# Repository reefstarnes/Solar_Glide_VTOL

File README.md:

# Solar_Glide_VTOL
Senior Capstone

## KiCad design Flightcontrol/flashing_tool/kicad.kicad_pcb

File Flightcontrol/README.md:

# Flight control
Flight Controller:

Flasher4OTG:

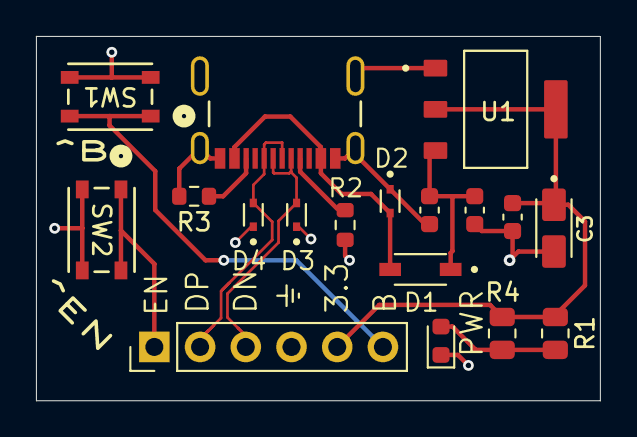
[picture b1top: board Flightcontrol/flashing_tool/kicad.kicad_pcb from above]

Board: 2 copper layers, 31.3 x 20.2 mm, 18 parts (0 on the bottom side), 11 nets.

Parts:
C1, C4: 0.1uF; C_0603_1608Metric
C2: 10uF; C_0603_1608Metric
C3: 22uF; CAPMP3216X180N
D1: 1N5819HW-7-F; SOD3715X145N
D2, D3, D4: LESD5D5.0CT1G; TVS_LESD5D5.0CT1G
J1: 2171790001; MOLEX_2171790001
J2: Conn_01x06_Pin; PinHeader_1x06_P2.54mm_Vertical
PWR: LED; LED_0603_1608Metric
R1, R4: 560; R_0805_2012Metric
R2, R3: 5.1k; R_0603_1608Metric
SW1, SW2: PTS815 SJM 250 SMTR LFS; GSPTS0020
U1: AMS1117-3.3; SOT229P700X180-4N

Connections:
/3.3: C3.1, C4.1, J2.5, R1.1, R4.1, U1.2 (VOUT)
/D+: D4.2, J1.A6 (DP1), J1.B6 (DP2), J2.2
/D-: D3.2, J1.A7 (DN1), J1.B7 (DN2), J2.3
/S1: J2.1, SW2.1, SW2.2
/S2: J2.6, SW1.1, SW1.2
/VCC_5V: C1.1, C2.1, D1.C, U1.3 (VIN)
GND: C1.2, C2.2, C3.2, C4.2, D2.1, D3.1, D4.1, J1.A1B12 (GND1), J1.B1A12 (GND2), J1.SH1 (SHIELD1), J1.SH2 (SHIELD2), J1.SH3 (SHIELD3), J1.SH4 (SHIELD4), J2.4, PWR.1 (K), R2.2, R3.2, SW1.3, SW1.4, SW2.3, SW2.4, U1.1 (GND/ADJ)
unnamed: PWR.2 (A), R1.2, R4.2
unnamed: J1.A5 (CC1), R2.1
unnamed: J1.B5 (CC2), R3.1
unnamed: D1.A, D2.2, J1.A4B9 (VBUS1), J1.B4A9 (VBUS2)

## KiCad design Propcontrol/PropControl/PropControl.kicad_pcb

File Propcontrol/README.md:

# Prop control
Prop control block

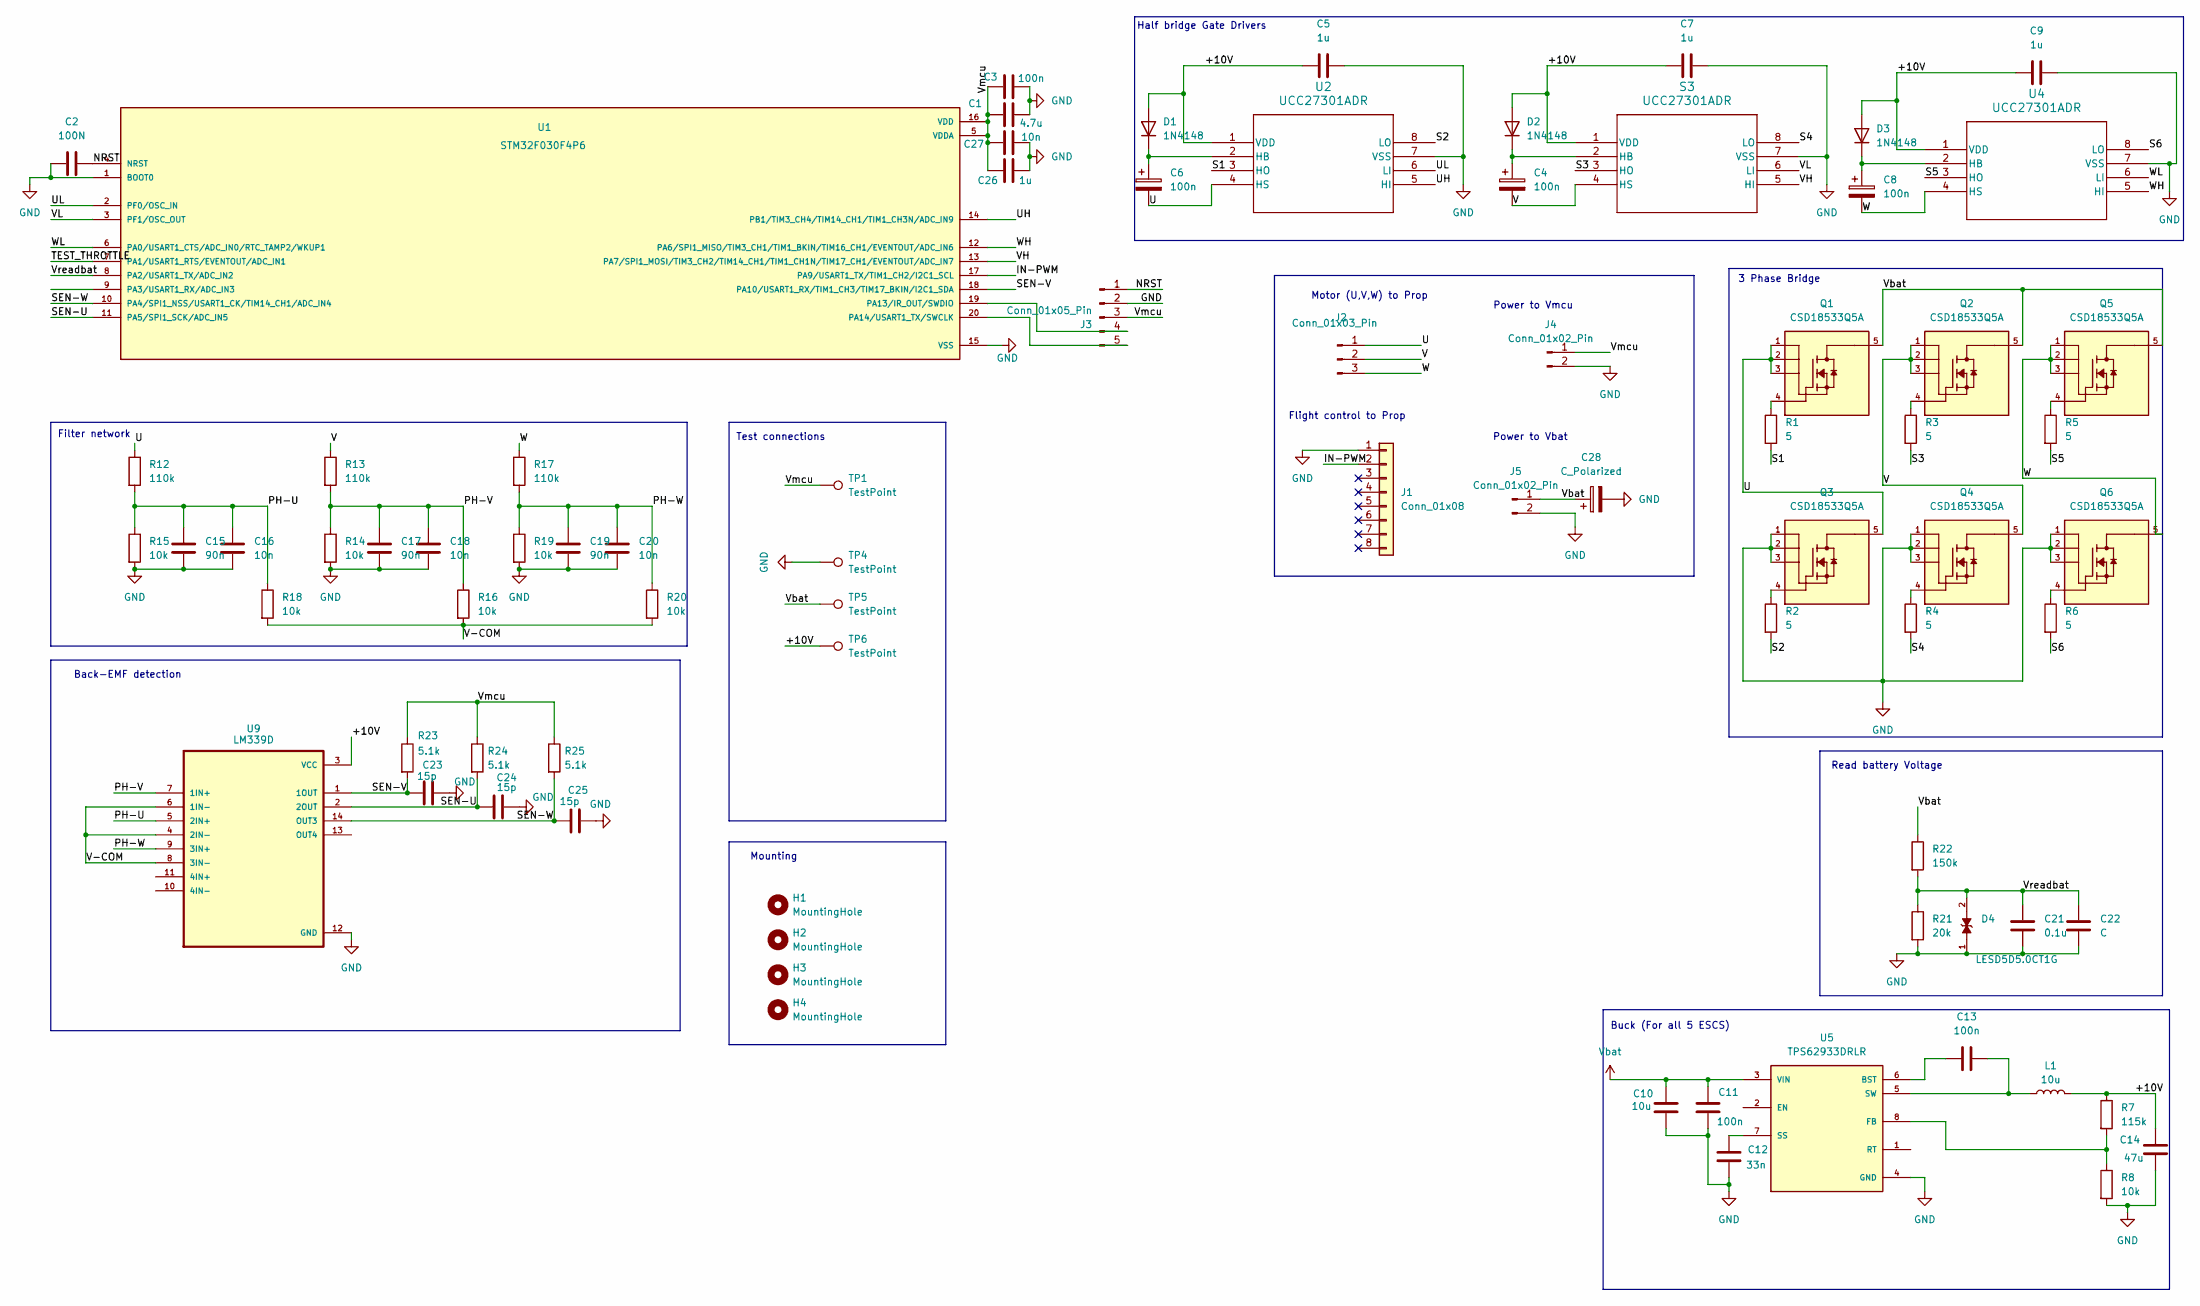
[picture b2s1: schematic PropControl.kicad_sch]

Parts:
C1: 4.7u; C_0603_1608Metric
C2: 100N; C_0603_1608Metric
C3: 100n; CAPC1608X90 100nF
C4, C6, C8, C11, C13: 100n; C_0603_1608Metric
C5, C7, C9, C27: 1u; C_0603_1608Metric
C10: 10u; C_0603_1608Metric
C12: 33n; C_1206_3216Metric
C14: 47u; C_1206_3216Metric
C15, C17, C19: 90n; CAPC1608X90 100nF
C16, C18, C20, C26: 10n; CAPC1608X90N 10nF
C21: 0.1u; C_0603_1608Metric
C22: C; C_0603_1608Metric
C23, C24, C25: 15p; C_0603_1608Metric
C28: C_Polarized; CP_Radial_D12.5mm_P5.00mm
D1, D2, D3: 1N4148; D_DO-35_SOD27_P7.62mm_Horizontal
D4: LESD5D5.0CT1G; TVS_LESD5D5.0CT1G; PARTREV O
H1, H2, H3, H4: MountingHole; MountingHole_2.2mm_M2
J1: Conn_01x08; CONN_SM06B-GHS-TB_JST
J2: Conn_01x03_Pin; MR60PW-M
J3: Conn_01x05_Pin; PinHeader_1x05_P2.54mm_Vertical
J4: Conn_01x02_Pin; JST_PH_B2B-PH-K_1x02_P2.00mm_Vertical
J5: Conn_01x02_Pin; AMASS_XT60-M_1x02_P7.20mm_Vertical
L1: 10u; L_0805_2012Metric
Q1, Q2, Q3, Q4, Q5, Q6: CSD18533Q5A; VSON-8_3.3x3.3mm_P0.65mm_NexFET; PARTREV B
R1, R2, R3, R4, R5, R6: 5; R_0603_1608Metric
R7: 115k; R_0805_2012Metric
R8, R14, R15, R16, R18, R19, R20: 10k; R_0603_1608Metric
R12, R13, R17: 110k; R_1206_3216Metric
R21: 20k; R_0603_1608Metric
R22: 150k; R_0603_1608Metric
R23, R24, R25: 5.1k; R_0603_1608Metric
S3: UCC27301ADR; SOIC8_D_TEX
TP1, TP4, TP5, TP6: TestPoint; TestPoint_Pad_D1.5mm
U1: STM32F030F4P6; SOP65P640X120-20N
U2, U4: UCC27301ADR; SOIC8_D_TEX
U5: TPS62933DRLR; SOTFL50P160X60-8N; PARTREV D
U9: LM339D; SOIC127P600X175-14N

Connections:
/+10V: C5.1, C7.1, C9.1, C14.1, D1.2 (A), D2.2 (A), D3.2 (A), L1.2, R7.1, S3.1 (VDD), TP6.1, U2.1 (VDD), U4.1 (VDD), U9.3 (VCC)
/IN-PWM: J1.2, U1.17 (PA9/USART1_TX/TIM1_CH2/I2C1_SCL)
/NRST: C2.2, J3.1, U1.4 (NRST)
/PH-U: C15.1, C16.1, R12.2, R15.1, R18.1, U9.5 (2IN+)
/PH-V: C17.1, C18.1, R13.2, R14.1, R16.1, U9.7 (1IN+)
/PH-W: C19.1, C20.1, R17.2, R19.1, R20.1, U9.9 (3IN+)
/S1: R1.2, U2.3 (HO)
/S2: R2.2, U2.8 (LO)
/S3: R3.2, S3.3 (HO)
/S4: R4.2, S3.8 (LO)
/S5: R5.2, U4.3 (HO)
/S6: R6.2, U4.8 (LO)
/SEN-U: C24.1, R24.2, U1.11 (PA5/SPI1_SCK/ADC_IN5), U9.2 (2OUT)
/SEN-V: C23.1, R23.2, U1.18 (PA10/USART1_RX/TIM1_CH3/TIM17_BKIN/I2C1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), U9.1 (1OUT)
/SEN-W: C25.1, R25.2, U1.10 (PA4/SPI1_NSS/USART1_CK/TIM14_CH1/ADC_IN4), U9.14 (OUT3)
/TEST_THROTTLE: U1.7 (PA1/USART1_RTS/EVENTOUT/ADC_IN1)
/U: C6.2, J2.1, Q1.1, Q1.2, Q1.3, Q3.5, R12.1, U2.4 (HS)
/UH: U1.14 (PB1/TIM3_CH4/TIM14_CH1/TIM1_CH3N/ADC_IN9), U2.5 (HI)
/UL: U1.2 (PF0/OSC_IN), U2.6 (LI)
/V: C4.2, J2.2, Q2.1, Q2.2, Q2.3, Q4.5, R13.1, S3.4 (HS)
/V-COM: R16.2, R18.2, R20.2, U9.4 (2IN-), U9.6 (1IN-), U9.8 (3IN-)
/VH: S3.5 (HI), U1.13 (PA7/SPI1_MOSI/TIM3_CH2/TIM14_CH1/TIM1_C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)
/VL: S3.6 (LI), U1.3 (PF1/OSC_OUT)
/Vmcu: C1.1, C3.1, C26.1, C27.1, J3.3, J4.1, R23.1, R24.1, R25.1, TP1.1, U1.5 (VDDA), U1.16 (VDD)
/Vreadbat: C21.1, C22.1, D4.2, R21.1, R22.2, U1.8 (PA2/USART1_TX/ADC_IN2)
/W: C8.2, J2.3, Q5.1, Q5.2, Q5.3, Q6.5, R17.1, U4.4 (HS)
/WH: U1.12 (PA6/SPI1_MISO/TIM3_CH1/TIM1_BKIN/TIM16_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), U4.5 (HI)
/WL: U1.6 (PA0/USART1_CTS/ADC_IN0/RTC_TAMP2/WKUP1), U4.6 (LI)
GND: C1.2, C2.1, C3.2, C5.2, C7.2, C9.2, C10.2, C11.2, C12.2, C14.2, C15.2, C16.2, C17.2, C18.2, C19.2, C20.2, C21.2, C22.2, C23.2, C24.2, C25.2, C26.2, C27.2, C28.2, D4.1, J1.1, J3.2, J4.2, J5.2, Q3.1, Q3.2, Q3.3, Q4.1, Q4.2, Q4.3, Q6.1, Q6.2, Q6.3, R8.2, R14.2, R15.2, R19.2, R21.2, S3.7 (VSS), TP4.1, U1.1 (BOOT0), U1.15 (VSS), U2.7 (VSS), U4.7 (VSS), U5.4 (GND), U9.12 (GND)
unnamed: C6.1, D1.1 (K), U2.2 (HB)
unnamed: C4.1, D2.1 (K), S3.2 (HB)
unnamed: C8.1, D3.1 (K), U4.2 (HB)
unnamed: J3.4, U1.19 (PA13/IR_OUT/SWDIO)
unnamed: J3.5, U1.20 (PA14/USART1_TX/SWCLK)
unnamed: Q1.4, R1.1
unnamed: Q2.4, R3.1
unnamed: Q3.4, R2.1
unnamed: Q4.4, R4.1
unnamed: Q5.4, R5.1
unnamed: Q6.4, R6.1
unnamed: C13.1, U5.6 (BST)
unnamed: R7.2, R8.1, U5.8 (FB)
unnamed: C12.1, U5.7 (SS)
unnamed: C13.2, L1.1, U5.5 (SW)
Vbat: C10.1, C11.1, C28.1, J5.1, Q1.5, Q2.5, Q5.5, R22.1, TP5.1, U5.3 (VIN)

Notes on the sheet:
Flight control to Prop
Power to Vmcu
Mounting
Power to Vbat
Test connections
Half bridge Gate Drivers
Buck (For all 5 ESCS)
3 Phase Bridge
Back-EMF detection
Motor (U,V,W) to Prop
Read battery Voltage
Filter network

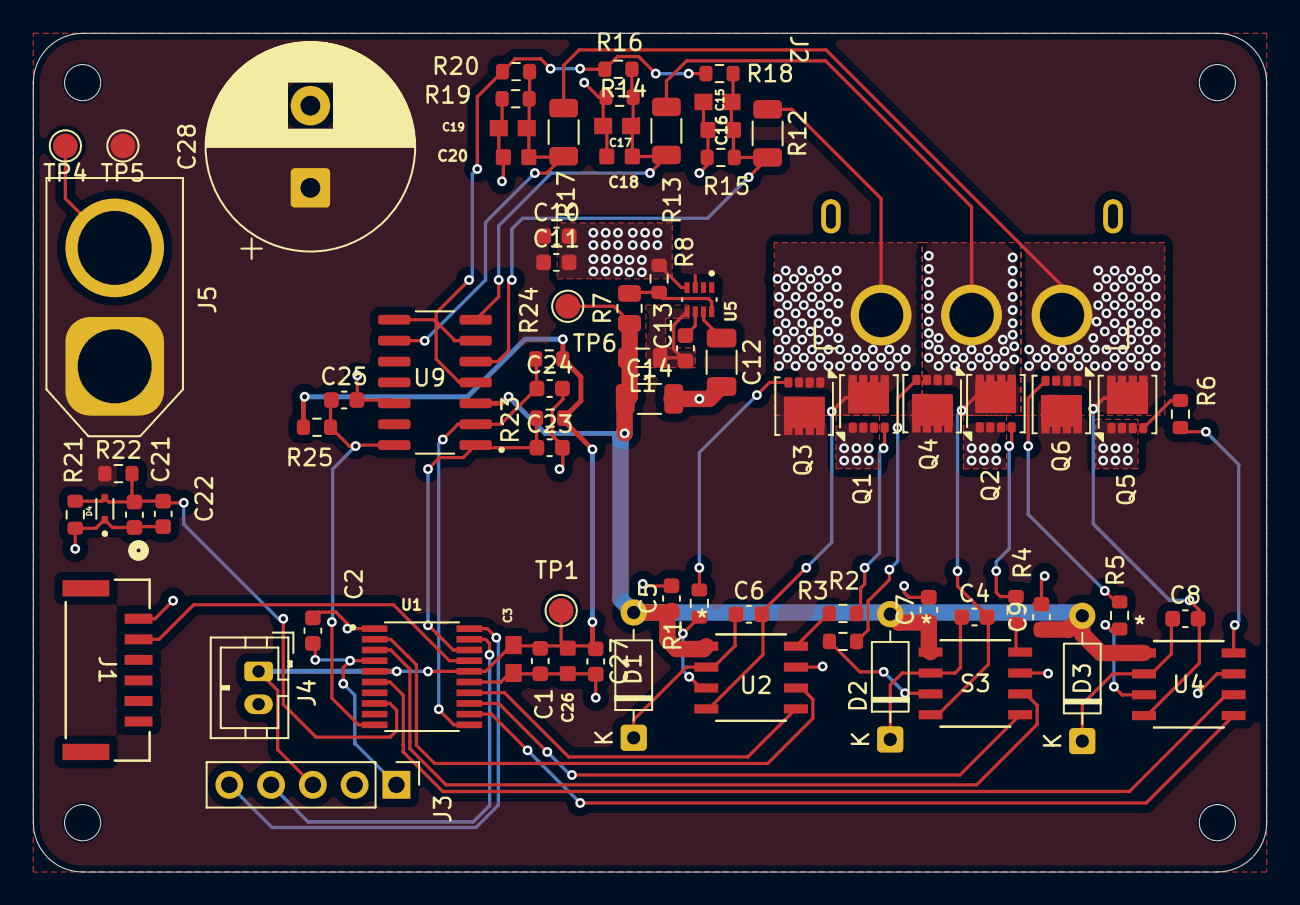
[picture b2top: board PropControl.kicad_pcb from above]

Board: 2 copper layers, 75.0 x 51.0 mm, 80 parts (0 on the bottom side), 44 nets.

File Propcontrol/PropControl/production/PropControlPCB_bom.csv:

Designator,Footprint,Quantity,Value,LCSC Part #
C1,0603,1,4.7u,
C10,0603,1,10u,
"C11, C13, C2, C4, C6, C8",0603,6,100n,
C12,1206,1,33n,
C14,1206,1,47u,
"C15, C17, C19",CAPC1608X90 100nF,3,90n,
"C16, C18, C20, C26",CAPC1608X90N 10nF,4,10n,
C21,0603,1,0.1u,
C22,0603,1,C,
"C23, C24, C25",0603,3,15p,
"C27, C5, C7, C9",0603,4,1u,
C28,CP_Radial_D12.5mm_P5.00mm,1,C_Polarized,
C3,CAPC1608X90 100nF,1,100n,
"D1, D2, D3",D_DO-35_SOD27_P7.62mm_Horizontal,3,1N4148,
D4,TVS_LESD5D5.0CT1G,1,LESD5D5.0CT1G,
J1,CONN_SM06B-GHS-TB_JST,1,Conn_01x08,
J2,MR60PW-M,1,Conn_01x03_Pin,
J3,PinHeader_1x05_P2.54mm_Vertical,1,Conn_01x05_Pin,
J4,JST_PH_B2B-PH-K_1x02_P2.00mm_Vertical,1,Conn_01x02_Pin,
J5,AMASS_XT60-M_1x02_P7.20mm_Vertical,1,Conn_01x02_Pin,
L1,0805,1,10u,
"Q1, Q2, Q3, Q4, Q5, Q6",VSON-8_3.3x3.3mm_P0.65mm_NexFET,6,CSD18533Q5A,
"R1, R2, R3, R4, R5, R6",0603,6,5,
"R12, R13, R17",1206,3,110k,
"R14, R15, R16, R18, R19, R20, R8",0603,7,10k,
R21,0603,1,20k,
R22,0603,1,150k,
"R23, R24, R25",0603,3,5.1k,
R7,0805,1,115k,
"S3, U2, U4",SOIC8_D_TEX,3,UCC27301ADR,
"TP1, TP4, TP5, TP6",TestPoint_Pad_D1.5mm,4,TestPoint,
U1,SOP65P640X120-20N,1,STM32F030F4P6,
U5,SOTFL50P160X60-8N,1,TPS62933DRLR,
U9,SOIC127P600X175-14N,1,LM339D,

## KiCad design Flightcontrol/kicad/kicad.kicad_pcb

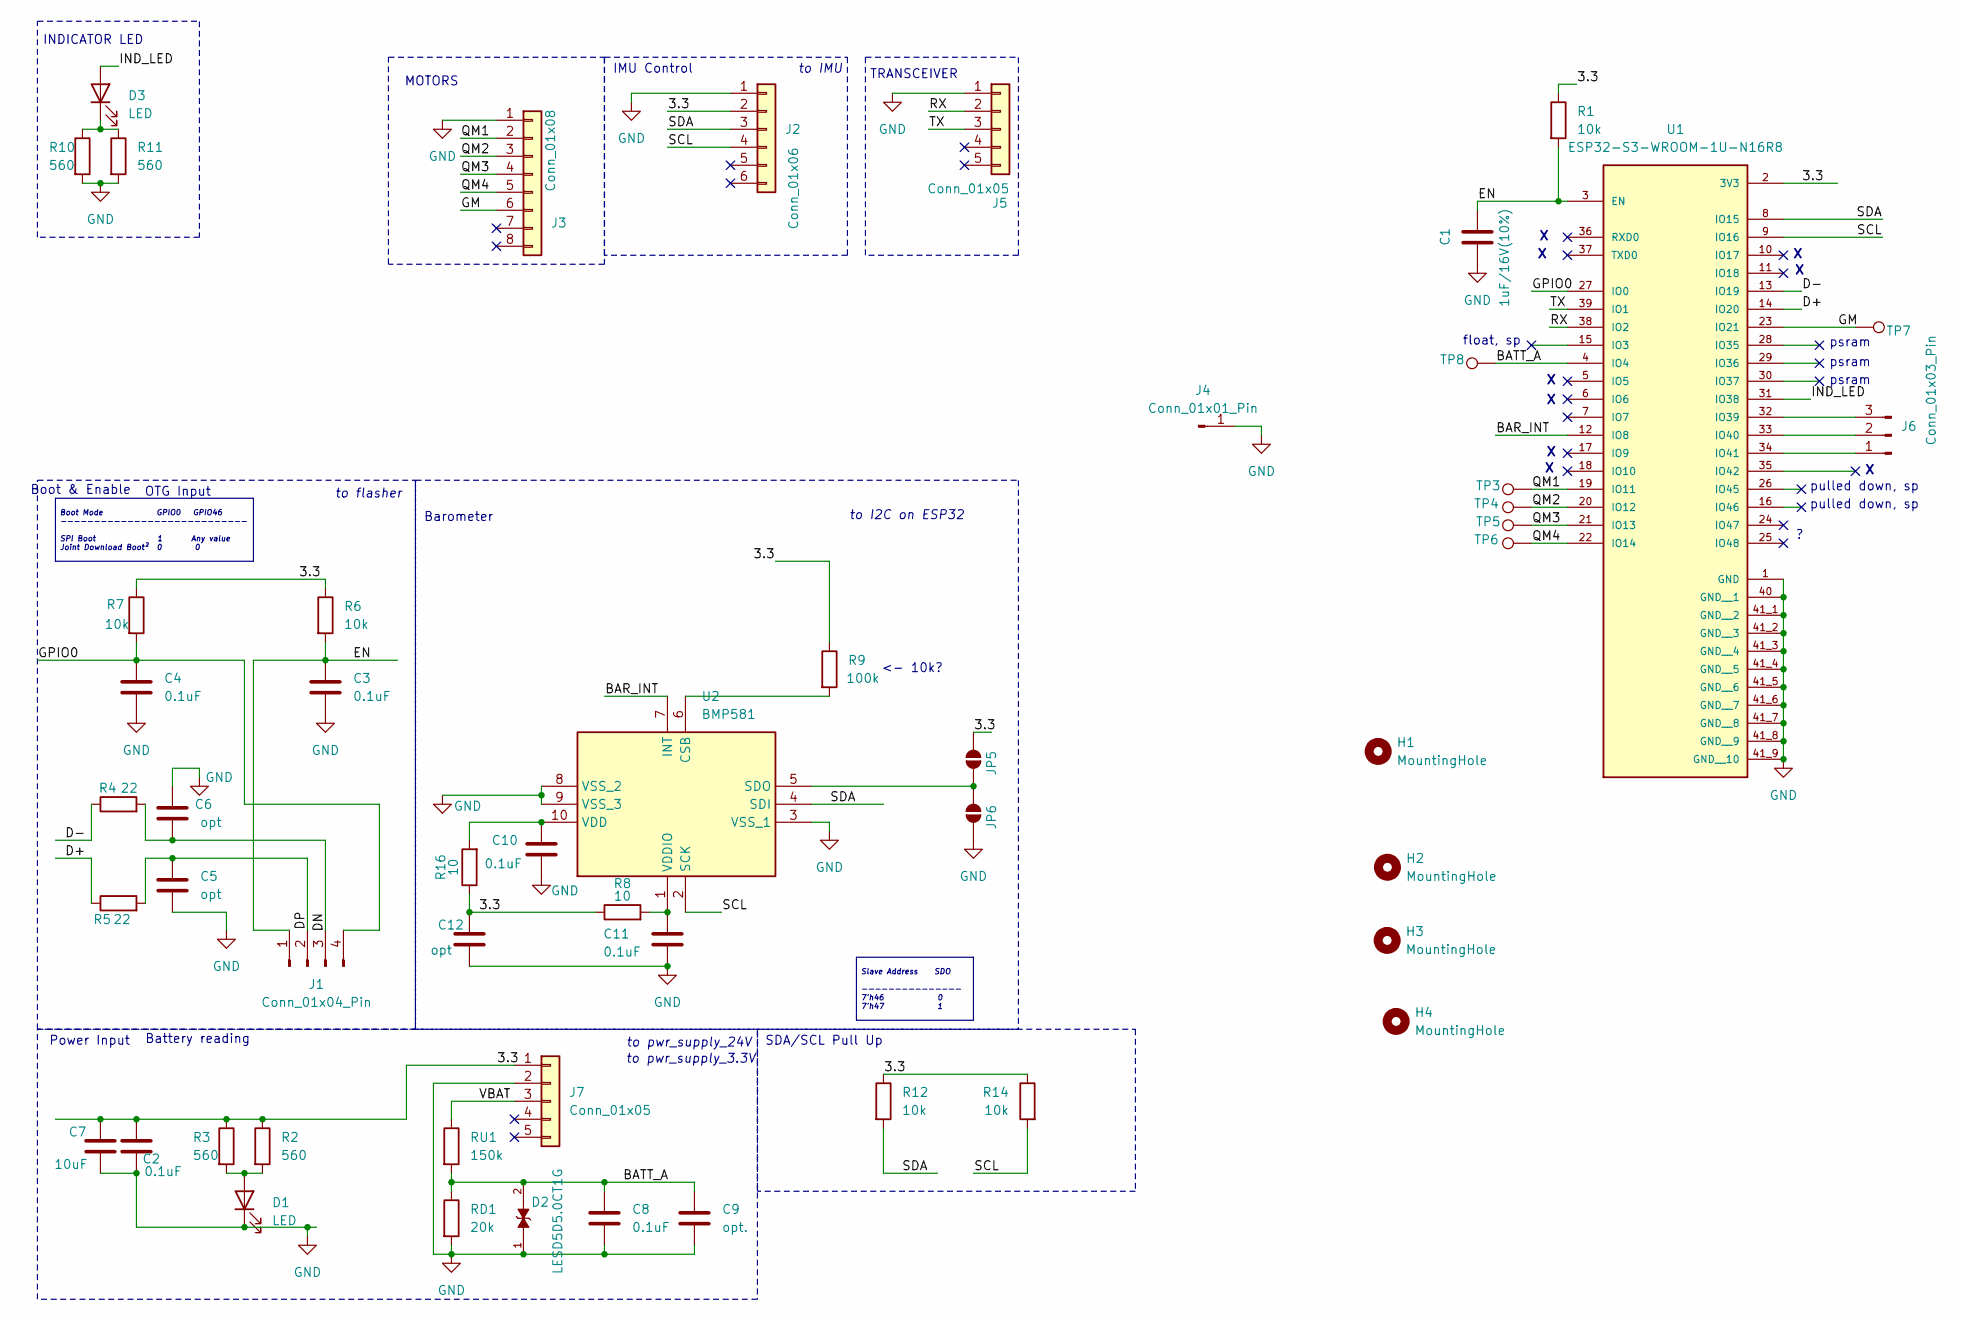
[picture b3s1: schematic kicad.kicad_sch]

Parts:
C1: 1uF/16V(10%); C_0603_1608Metric
C2, C3, C4, C8, C10, C11: 0.1uF; C_0603_1608Metric
C5, C6, C12: opt; C_0603_1608Metric
C7: 10uF; C_0603_1608Metric
C9: opt.; C_0603_1608Metric
D1, D3: LED; LED_0603_1608Metric
D2: LESD5D5.0CT1G; TVS_LESD5D5.0CT1G; PARTREV O
H1, H2, H3, H4: MountingHole; MountingHole_2.2mm_M2
J1: Conn_01x04_Pin; PinHeader_1x04_P2.54mm_Vertical
J2: Conn_01x06; CONN_CCSH-W10R-04TR-BK-A_ADA
J3: Conn_01x08; CONN_SM06B-GHS-TB_JST
J4: Conn_01x01_Pin; PinHeader_1x01_P2.54mm_Vertical
J5, J7: Conn_01x05; CONN_SM03B-GHS-TBLFSN_JST
J6: Conn_01x03_Pin; PinHeader_1x03_P2.54mm_Vertical
JP5, JP6: SolderJumper_2_Open; SolderJumper-2_P1.3mm_Open_RoundedPad1.0x1.5mm
R1, R6, R7, R12, R14: 10k; R_0603_1608Metric
R2, R3, R10, R11: 560; R_0805_2012Metric
R4, R5: 22; R_0603_1608Metric
R8, R16: 10; R_0603_1608Metric
R9: 100k; R_0603_1608Metric
RD1: 20k; R_0805_2012Metric
RU1: 150k; R_0603_1608Metric
TP3, TP5, TP7, TP8: x; TestPoint_Pad_D1.5mm
TP4, TP6: BAR_CLK; TestPoint_Pad_D1.5mm
U1: ESP32-S3-WROOM-1U-N16R8; ESP32-S3-WROOM-1U; PARTREV v1.1
U2: BMP581; Mouser Part Number 262-BMP581

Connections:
/3.3: C2.1, C7.1, C12.1, J2.2, J7.1, JP5.2 (B), R1.1, R2.1, R3.1, R6.1, R7.1, R8.1, R9.1, R12.1, R14.1, R16.1, U1.2 (3V3)
/BAR_INT: U1.12 (IO8), U2.7 (INT)
/BATT_A: C8.1, C9.1, D2.2, RD1.1, RU1.2, TP8.1, U1.4 (IO4)
/D+: R5.1, U1.14 (IO20)
/D-: R4.1, U1.13 (IO19)
/DN: C6.2, J1.3, R4.2
/DP: C5.1, J1.2, R5.2
/EN: C1.1, C3.1, J1.1, R1.2, R6.2, U1.3 (EN)
/GM: J3.6, TP7.1, U1.23 (IO21)
/GPIO0: C4.1, J1.4, R7.2, U1.27 (IO0)
/IND_LED: D3.2 (A), U1.31 (IO38)
/QM1: J3.2, TP3.1, U1.19 (IO11)
/QM2: J3.3, TP4.1, U1.20 (IO12)
/QM3: J3.4, TP5.1, U1.21 (IO13)
/QM4: J3.5, TP6.1, U1.22 (IO14)
/RX: J5.2, U1.38 (IO2)
/SCL: J2.4, R14.2, U1.9 (IO16), U2.2 (SCK)
/SDA: J2.3, R12.2, U1.8 (IO15), U2.4 (SDI)
/TX: J5.3, U1.39 (IO1)
/VBAT: J7.3, RU1.1
GND: C1.2, C2.2, C3.2, C4.2, C5.2, C6.1, C7.2, C8.2, C9.2, C10.2, C11.2, C12.2, D1.1 (K), D2.1, J2.1, J3.1, J4.1, J5.1, J7.2, JP6.1 (A), R10.2, R11.2, RD1.2, U1.1 (GND), U1.40 (GND__1), U1.41, U1.41_1 (GND__2), U1.41_2 (GND__3), U1.41_3 (GND__4), U1.41_4 (GND__5), U1.41_5 (GND__6), U1.41_6 (GND__7), U1.41_7 (GND__8), U1.41_8 (GND__9), U1.41_9 (GND__10), U2.3 (VSS_1), U2.8 (VSS_2), U2.9 (VSS_3)
unnamed: D1.2 (A), R2.2, R3.2
unnamed: D3.1 (K), R10.1, R11.1
unnamed: J6.1, U1.34 (IO41)
unnamed: J6.2, U1.33 (IO40)
unnamed: J6.3, U1.32 (IO39)
unnamed: JP5.1 (A), JP6.2 (B), U2.5 (SDO)
unnamed: R9.2, U2.6 (CSB)
unnamed: C10.1, R16.2, U2.10 (VDD)
unnamed: C11.1, R8.2, U2.1 (VDDIO)

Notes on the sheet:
to pwr_supply_24V
OTG Input
to IMU
MOTORS
Barometer
float, sp
Battery reading
Power Input
to I2C on ESP32
psram
to pwr_supply_3.3V
Boot & Enable
<- 10k?
pulled down, sp
TRANSCEIVER
IMU Control
INDICATOR LED
to flasher
SDA/SCL Pull Up
Slave Address SDO --------------- 7'h46 0 7'h47 1
Boot Mode GPIO0 GPIO46 ---------------------------- SPI Boot 1 Any value Joint Download Boot² 0 0

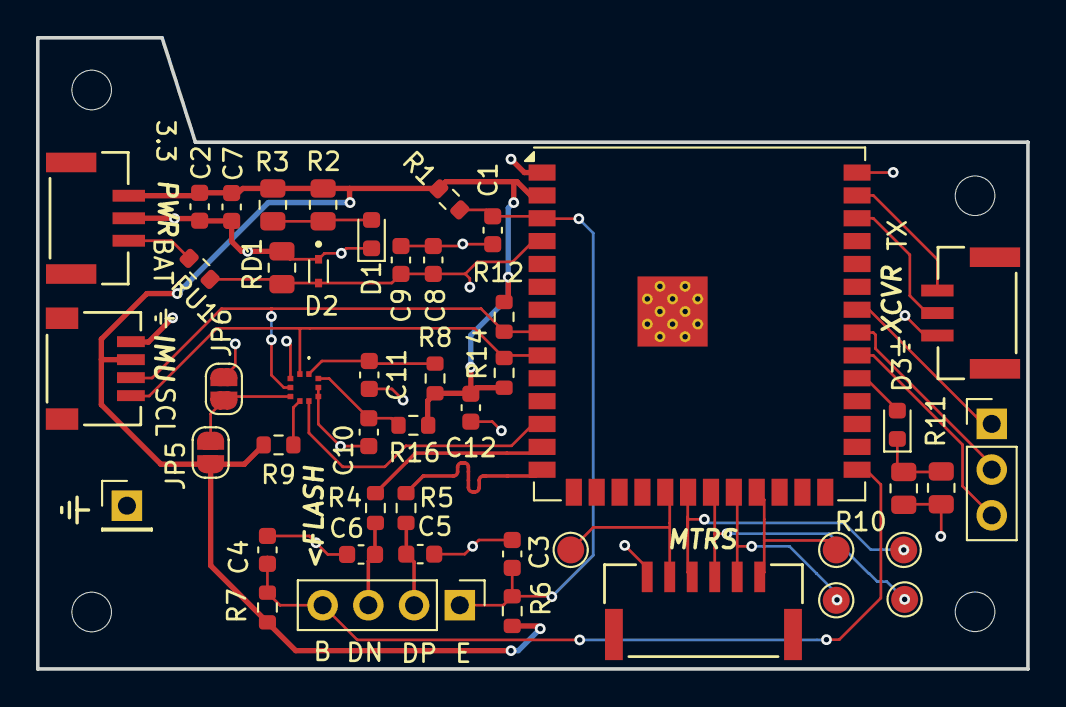
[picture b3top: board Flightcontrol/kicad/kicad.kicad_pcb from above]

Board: 2 copper layers, 55.0 x 35.1 mm, 52 parts (1 on the bottom side), 30 nets.

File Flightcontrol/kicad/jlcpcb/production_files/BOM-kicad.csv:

Comment,Designator,Footprint,LCSC,Quantity
22,R5,R_0603_1608Metric,,1
10,R8,R_0603_1608Metric,,1
0.1uF,C3,C_0603_1608Metric,,1
LESD5D5.0CT1G,D2,TVS_LESD5D5.0CT1G,,1
Conn_01x08,J3,CONN_SM06B-GHS-TB_JST,,1
Conn_01x06,J2,CONN_CCSH-W10R-04TR-BK-A_ADA,,1
Conn_01x04_Pin,J1,PinHeader_1x04_P2.54mm_Vertical,,1
22,R4,R_0603_1608Metric,,1
0.1uF,C2,C_0603_1608Metric,,1
LED,D1,LED_0603_1608Metric,,1
x,TP7,TestPoint_Pad_D1.5mm,,1
10uF,C7,C_0603_1608Metric,,1
10k,R12,R_0603_1608Metric,,1
1uF/16V(10%),C1,C_0603_1608Metric,,1
10k,R1,R_0603_1608Metric,,1
0.1uF,C4,C_0603_1608Metric,,1
x,TP3,TestPoint_Pad_D1.5mm,,1
opt.,C9,C_0603_1608Metric,,1
100k,R9,R_0603_1608Metric,,1
0.1uF,C10,C_0603_1608Metric,,1
LED,D3,LED_0603_1608Metric,,1
560,R2,R_0805_2012Metric,,1
Conn_01x05,J7,CONN_SM03B-GHS-TBLFSN_JST,,1
BAR_CLK,TP4,TestPoint_Pad_D1.5mm,,1
x,TP5,TestPoint_Pad_D1.5mm,,1
Conn_01x03_Pin,J6,PinHeader_1x03_P2.54mm_Vertical,,1
560,R3,R_0805_2012Metric,,1
Conn_01x05,J5,CONN_SM03B-GHS-TBLFSN_JST,,1
10k,R7,R_0603_1608Metric,,1
20k,RD1,R_0805_2012Metric,,1
opt,C12,C_0603_1608Metric,,1
150k,RU1,R_0603_1608Metric,,1
BAR_CLK,TP6,TestPoint_Pad_D1.5mm,,1
560,R11,R_0805_2012Metric,,1
opt,C5,C_0603_1608Metric,,1
560,R10,R_0805_2012Metric,,1
Conn_01x01_Pin,J4,PinHeader_1x01_P2.54mm_Vertical,,1
10k,R14,R_0603_1608Metric,,1
opt,C6,C_0603_1608Metric,,1
BMP581,U2,BMP581,,1
ESP32-S3-WROOM-1U-N16R8,U1,ESP32-S3-WROOM-1U,,1
0.1uF,C11,C_0603_1608Metric,,1
10k,R6,R_0603_1608Metric,,1
0.1uF,C8,C_0603_1608Metric,,1
10,R16,R_0603_1608Metric,,1
x,TP8,TestPoint_Pad_D1.5mm,,1

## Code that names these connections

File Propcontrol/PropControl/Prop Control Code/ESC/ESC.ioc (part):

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Mcu.Name=STM32F030F4Px
Mcu.Package=TSSOP20
Mcu.UserName=STM32F030F4Px
PA0.Signal=GPIO_Output
PA10.Signal=GPIO_Input
PA4.Signal=GPIO_Input
PA5.Signal=GPIO_Input
PA6.Signal=S_TIM3_CH1
PA7.Signal=S_TIM3_CH2
PA9.Signal=S_TIM1_CH2
PB1.Signal=S_TIM3_CH4
PF0-OSC_IN.Signal=GPIO_Output
PF1-OSC_OUT.Signal=GPIO_Output
board=custom

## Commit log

2025-10-26 setup
2025-10-26 begun schematic :)
2025-10-27 begun usbc programmer
2025-10-30 moved flash tool to seperate kicad file
2025-11-05 flasher4otg V1 finished
2025-11-05 Add image to Flight control README
2025-11-06 finished main schematic
2025-11-08 backing up for personal reasons
2025-11-10 sanity backup
2025-11-10 FC.V1 PCB Layout completed
2025-11-10 generated pcb files :)
2025-11-10 Update README with Flight Controller and Flasher4OTG images
2025-11-10 Replace image in README.md for Flight control
2025-11-11 V1 PC Schematic and PCB Finished
2025-11-24 BMP581 tested, works!
2025-12-02 test code fully implimented minus sending telemetry data
2026-01-29 changes january 29th
2026-05-02 added esc testcode for debug
2026-05-02 Init commit
2026-05-02 added simulation circuit diagram for comm
2026-05-05 implimented motor control via comm
2026-05-06 calibrated IMU & added gyro logging
2026-05-06 false readings of IMU now return old valid readings
2026-05-06 implimented kill switch
2026-05-06 throttles up to 0.5
2026-05-06 mapped steer channel data to -1 to 1
2026-05-06 added filtering for gyro data
2026-05-06 initial testing
2026-05-06 more bug fixes to PID
2026-05-06 even more bug fixes to PID
2026-05-07 newer changes
2026-05-18 updates to PIDs gain
